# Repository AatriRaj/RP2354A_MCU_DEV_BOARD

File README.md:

# RP2354A MCU Development Board

A custom microcontroller-board design built around the **Raspberry Pi RP2354A**, created in KiCad. The schematic includes USB-C connectivity, a 12 MHz crystal, a 3.3 V LDO regulator, boot/reset controls, status indication, and header connections for accessing board signals.

## Project Overview

The goal of this project is to develop a compact RP2354A-based hardware platform for embedded development, prototyping, and experimentation with the RP235x microcontroller family.

## Main Hardware Blocks

- **RP2354A MCU** — the main processing device.
- **USB Type-C connector** — provides the USB connection; the exact power/data behavior should be confirmed against the complete schematic and PCB.
- **12 MHz crystal** — external clock source for the MCU.
- **LD39200PU33R LDO** — 3.3 V regulation.
- **Boot switch** — supports entering the MCU's boot mode when implemented according to the RP2354A documentation.
- **Reset switch** — provides a manual reset control.
- **Status LED** — visual indication for firmware-controlled status or power, depending on its final connection.
- **Passives and decoupling capacitors** — support clock, power, USB, and general circuit operation.
- **Expansion headers** — provide access to selected signals for prototyping and debugging.

## Design Tools

- **Schematic capture:** KiCad
- **Design file supplied:** `RP2354A_MCU.kicad_sch`

## Repository Structure

```text
.
├── README.md
└── RP2354A_MCU.kicad_sch
```

Add the KiCad PCB layout (`.kicad_pcb`), project file (`.kicad_pro`), libraries, fabrication outputs, and firmware source as they become available.

## Opening the Design

1. Install KiCad.
2. Open `RP2354A_MCU.kicad_sch` in **Schematic Editor**.
3. Review the schematic and run **Electrical Rules Checker (ERC)**.
4. Once the PCB layout is available, review footprints and pin mapping, then run **Design Rules Checker (DRC)** before fabrication.

## Before Fabrication

This repository currently documents the supplied schematic, not a verified or production-ready board. Before ordering PCBs:

- Check the RP2354A pin assignments, power rails, decoupling, boot and reset circuitry against the current official datasheet and hardware-design guidance.
- Confirm the USB-C CC resistors, USB data-line routing/protection, and connector pin mapping.
- Verify the LDO input/output voltage limits, capacitor requirements, thermal dissipation, and current budget.
- Confirm the crystal's load-capacitance requirements and the selected capacitor values.
- Check that every required power pin is connected and that unused pins are handled correctly.
- Confirm whether external flash is required for the intended RP2354A configuration and include it if needed.
- Assign and verify all PCB footprints; inspect clearances, copper pours, return paths, and manufacturing constraints.
- Run ERC/DRC and perform a complete schematic-to-PCB connectivity review.

## Current Status

**Hardware schematic in progress.** The supplied file contains the MCU and supporting circuitry. PCB layout, firmware, validation results, and fabrication files are not included in the supplied project file.

## License

No license has been specified yet. Add a license before redistributing or reusing this design.

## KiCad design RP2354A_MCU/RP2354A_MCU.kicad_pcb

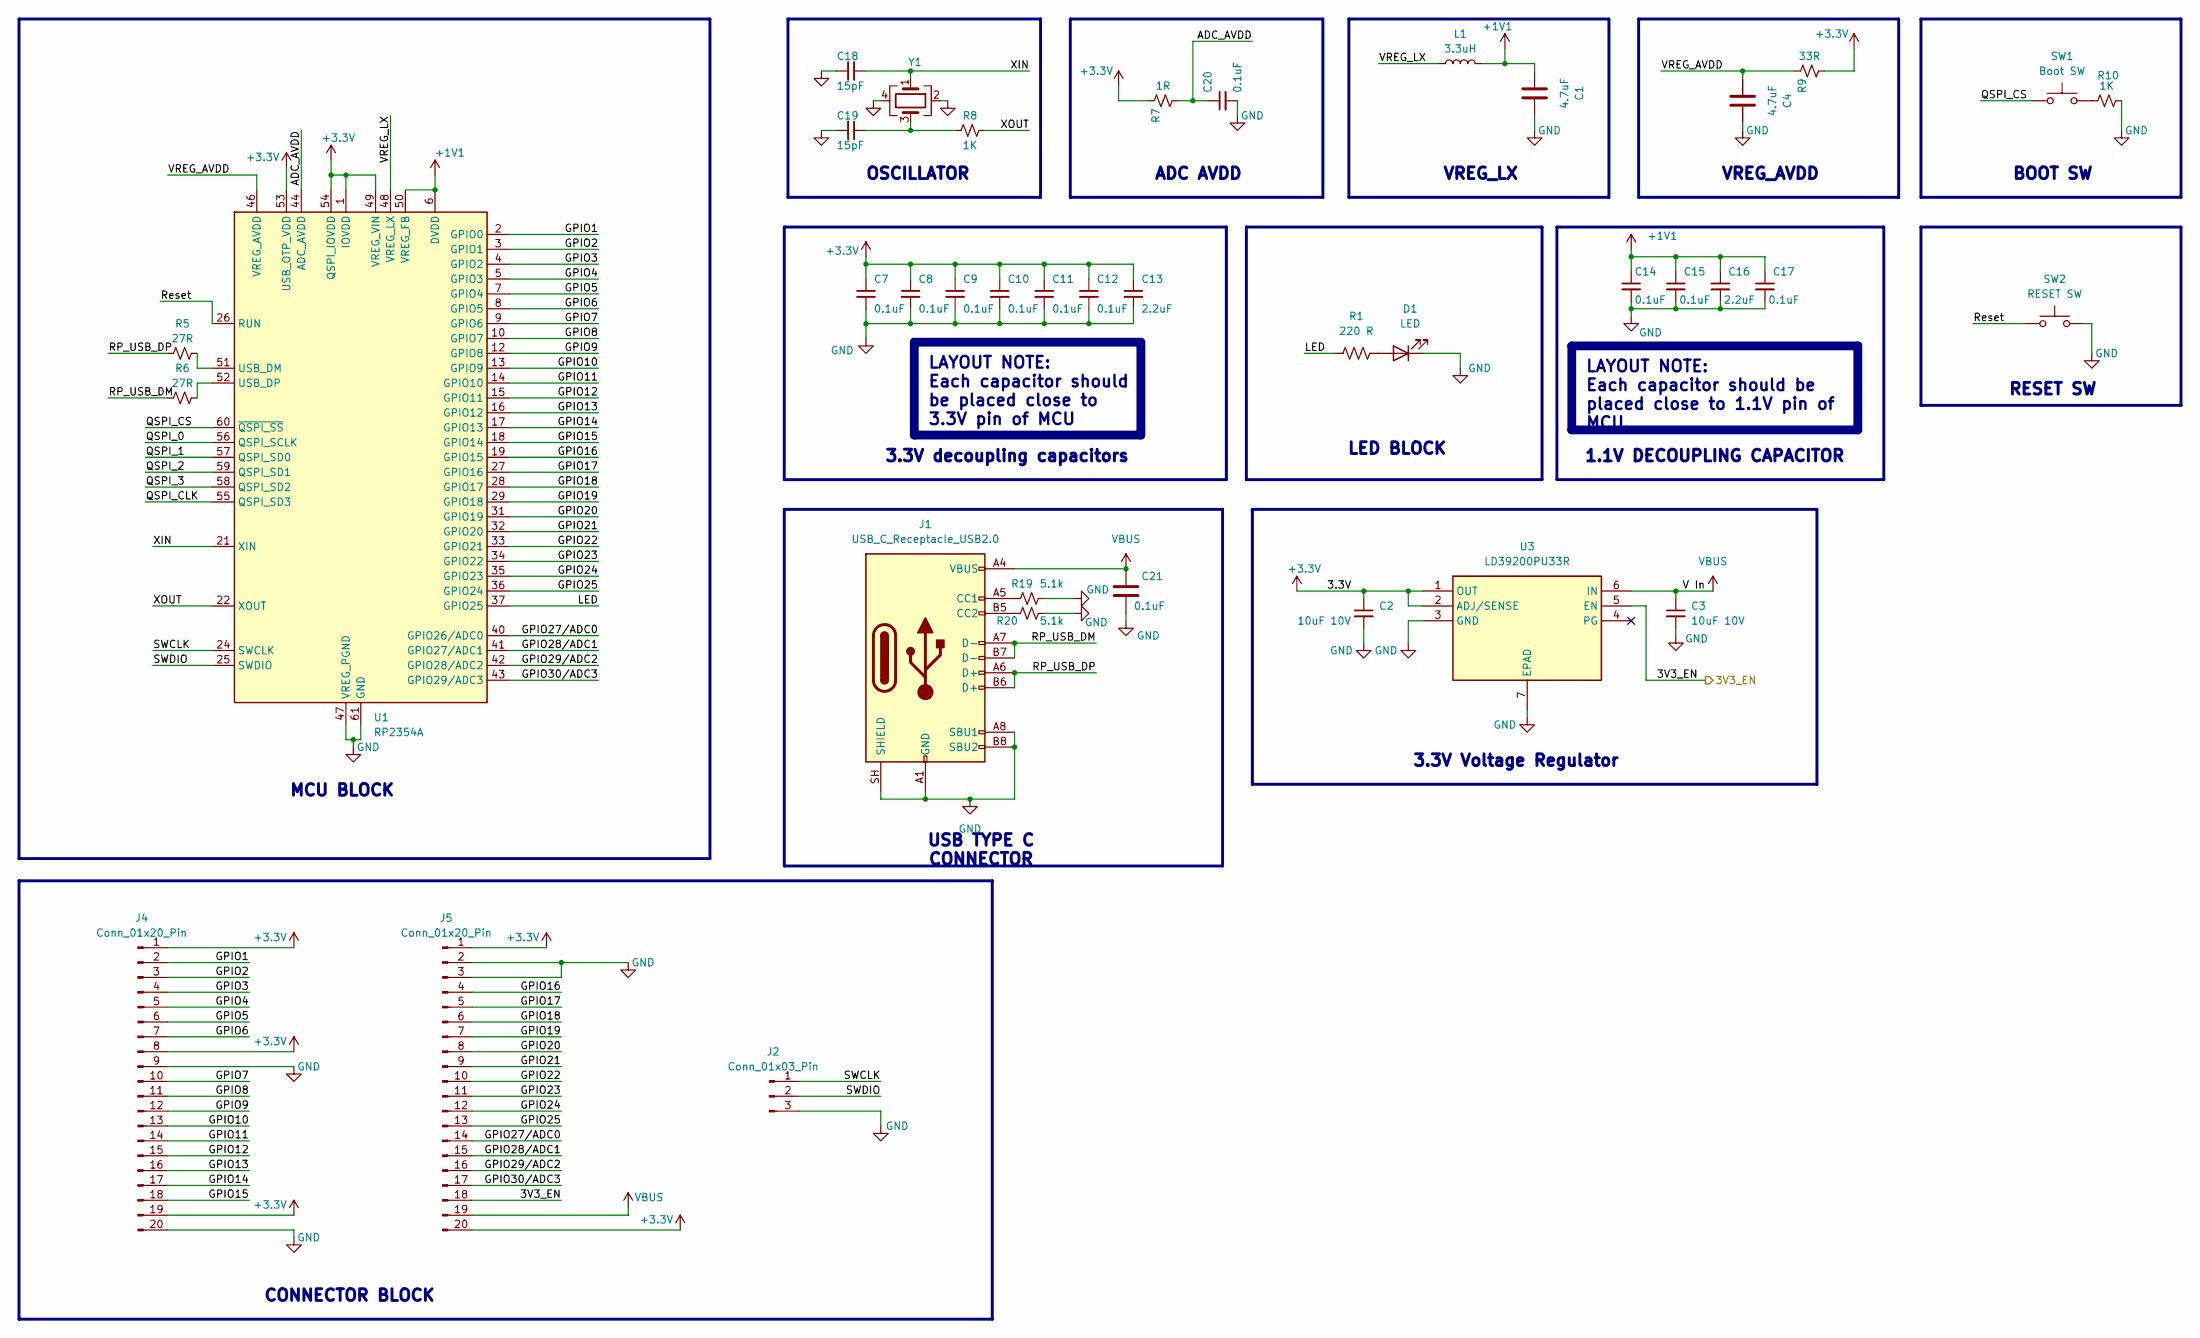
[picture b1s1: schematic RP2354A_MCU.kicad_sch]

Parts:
C1, C4: 4.7uF; C_0402_1005Metric
C2, C3: 10uF 10V; C_0805_2012Metric
C7, C8, C9, C10, C11, C12, C14, C15, C17, C20, C21: 0.1uF; C_0402_1005Metric
C13, C16: 2.2uF; C_0402_1005Metric
C18, C19: 15pF; C_0402_1005Metric
D1: LED; LED_0805_2012Metric
J1: USB_C_Receptacle_USB2.0; USB_C_Receptacle_GCT_USB4105-xx-A_16P_TopMnt_Horizontal
J2: Conn_01x03_Pin; PinHeader_1x03_P2.54mm_Vertical
J4: Conn_01x20_Pin; PinHeader_1x20_P2.54mm_Vertical
J5: Conn_01x20_Pin; PinHeader_1x20_P2.54mm_RP
L1: 3.3uH; L_0805_2012Metric
R1: 220 R; R_0402_1005Metric
R5, R6: 27R; R_0402_1005Metric
R7: 1R; R_0402_1005Metric
R8, R10: 1K; R_0402_1005Metric
R9: 33R; R_0402_1005Metric
R19, R20: 5.1k; R_0402_1005Metric
SW1: Boot SW; SW_SPST_B3U-1000P
SW2: RESET SW; SW_SPST_B3U-1000P
U1: RP2354A; QFN-60-1EP_7x7mm_P0.4mm_EP3.4x3.4mm
U3: LD39200PU33R; SON95P300X300X100-7N-D; Mouser Part Number 511-LD39200PU33R
Y1: ABM8-12.000MHZ-12-B1U-T; Crystal_SMD_3225-4Pin_3.2x2.5mm

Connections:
+1V1: C1.1, C14.1, C15.1, C16.1, C17.1, L1.2, U1.6 (DVDD), U1.23 (DVDD), U1.39 (DVDD), U1.50 (VREG_FB)
+3.3V: C2.1, C7.1, C8.1, C9.1, C10.1, C11.1, C12.1, C13.1, J4.1, J4.8, J4.19, J5.1, J5.20, R7.1, R9.2, U1.1 (IOVDD), U1.11 (IOVDD), U1.20 (IOVDD), U1.30 (IOVDD), U1.38 (IOVDD), U1.45 (IOVDD), U1.49 (VREG_VIN), U1.53 (USB_OTP_VDD), U1.54 (QSPI_IOVDD), U3.1 (OUT), U3.2 (ADJ/SENSE)
/3V3_EN: J5.18, U3.5 (EN)
/ADC_AVDD: C20.1, R7.2, U1.44 (ADC_AVDD)
/GPIO1: J4.2, U1.2 (GPIO0)
/GPIO2: J4.3, U1.3 (GPIO1)
/GPIO3: J4.4, U1.4 (GPIO2)
/GPIO4: J4.5, U1.5 (GPIO3)
/GPIO5: J4.6, U1.7 (GPIO4)
/GPIO6: J4.7, U1.8 (GPIO5)
/GPIO7: J4.10, U1.9 (GPIO6)
/GPIO8: J4.11, U1.10 (GPIO7)
/GPIO9: J4.12, U1.12 (GPIO8)
/GPIO10: J4.13, U1.13 (GPIO9)
/GPIO11: J4.14, U1.14 (GPIO10)
/GPIO12: J4.15, U1.15 (GPIO11)
/GPIO13: J4.16, U1.16 (GPIO12)
/GPIO14: J4.17, U1.17 (GPIO13)
/GPIO15: J4.18, U1.18 (GPIO14)
/GPIO16: J5.4, U1.19 (GPIO15)
/GPIO17: J5.5, U1.27 (GPIO16)
/GPIO18: J5.6, U1.28 (GPIO17)
/GPIO19: J5.7, U1.29 (GPIO18)
/GPIO20: J5.8, U1.31 (GPIO19)
/GPIO21: J5.9, U1.32 (GPIO20)
/GPIO22: J5.10, U1.33 (GPIO21)
/GPIO23: J5.11, U1.34 (GPIO22)
/GPIO24: J5.12, U1.35 (GPIO23)
/GPIO25: J5.13, U1.36 (GPIO24)
/GPIO27/ADC0: J5.14, U1.40 (GPIO26/ADC0)
/GPIO28/ADC1: J5.15, U1.41 (GPIO27/ADC1)
/GPIO29/ADC2: J5.16, U1.42 (GPIO28/ADC2)
/GPIO30/ADC3: J5.17, U1.43 (GPIO29/ADC3)
/LED: R1.1, U1.37 (GPIO25)
/QSPI_0: U1.56 (QSPI_SCLK)
/QSPI_1: U1.57 (QSPI_SD0)
/QSPI_2: U1.59 (QSPI_SD1)
/QSPI_3: U1.58 (QSPI_SD2)
/QSPI_CLK: U1.55 (QSPI_SD3)
/QSPI_CS: SW1.1, U1.60 (~QSPI_SS)
/RP_USB_DM: J1.A7 (D-), J1.B7 (D-), R6.1
/RP_USB_DP: J1.A6 (D+), J1.B6 (D+), R5.1
/Reset: SW2.1, U1.26 (RUN)
/SWCLK: J2.1, U1.24 (SWCLK)
/SWDIO: J2.2, U1.25 (SWDIO)
/VREG_AVDD: C4.1, R9.1, U1.46 (VREG_AVDD)
/VREG_LX: L1.1, U1.48 (VREG_LX)
/XIN: C18.1, U1.21 (XIN), Y1.1
/XOUT: R8.2, U1.22 (XOUT)
GND: C1.2, C2.2, C3.2, C4.2, C7.2, C8.2, C9.2, C10.2, C11.2, C12.2, C13.2, C14.2, C15.2, C16.2, C17.2, C18.2, C19.2, C20.2, C21.2, D1.1 (K), J1.A1 (GND), J1.A8 (SBU1), J1.A12 (GND), J1.B1 (GND), J1.B8 (SBU2), J1.B12 (GND), J1.SH (SHIELD), J2.3, J4.9, J4.20, J5.2, J5.3, R10.2, R19.2, R20.2, SW2.2, U1.47 (VREG_PGND), U1.61 (GND), U3.3 (GND), U3.7 (EPAD), Y1.2, Y1.4
unnamed: C19.1, R8.1, Y1.3
unnamed: D1.2 (A), R1.2
unnamed: J1.A5 (CC1), R19.1
unnamed: J1.B5 (CC2), R20.1
unnamed: R10.1, SW1.2
unnamed: R5.2, U1.51 (USB_DM)
unnamed: R6.2, U1.52 (USB_DP)
VBUS: C3.1, C21.1, J1.A4 (VBUS), J1.A9 (VBUS), J1.B4 (VBUS), J1.B9 (VBUS), J5.19, U3.6 (IN)

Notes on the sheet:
1.1V DECOUPLING CAPACITOR
LED BLOCK
CONNECTOR BLOCK
VREG_AVDD
MCU BLOCK
LAYOUT NOTE: Each capacitor should be placed close to 3.3V pin of MCU
3.3V Voltage Regulator
LAYOUT NOTE: Each capacitor should be placed close to 1.1V pin of MCU.
USB TYPE C CONNECTOR
VREG_LX
OSCILLATOR
RESET SW
BOOT SW
3.3V decoupling capacitors
ADC AVDD

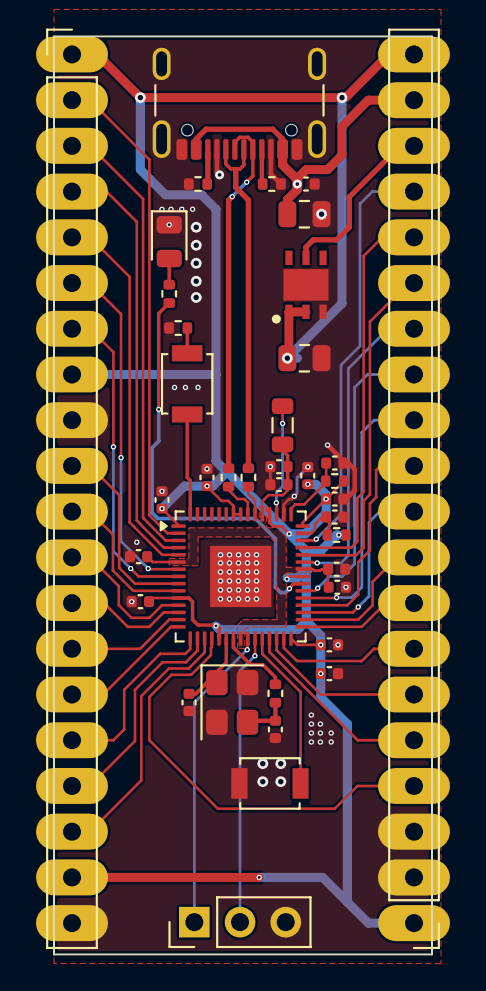
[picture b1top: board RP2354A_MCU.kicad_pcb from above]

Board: 2 copper layers, 21.0 x 51.0 mm, 39 parts (0 on the bottom side), 53 nets.
